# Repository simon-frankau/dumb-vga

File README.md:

# A simple flash-based VGA display

![A picture of a cat's head, surrounded by a kind of sunburst pattern,
being displayed on a montior](./demo.jpg)

The idea of this project is to generate a basic VGA-like signal that a
monitor will display by putting the signal in a flash memory, and then
using counters to run through the address space. Simple, eh?

## VGA signal timing

We have h-sync and v-sync signals, with their respective front and
back porches. The main trick is the find a resolution that fits nicely
into a flash memory, so that the flash memory is a multiple of the
screen size - not the visible screen size, but the screen size with
all the sync bits.

A bit of twiddling gives a 384x240 visible display that is 512x256
once all the sync etc. is factored in.

## Clocking

A 32MHz clock is used as a dot clock for a 768x480 image at 60 FPS
(1024x512 when sync signals are factored in). The Flash cannot handle
a 32MHz data rate, but we clock it every other cycle and do scan-line
doubling to display a 384x240 image.

## VGA levels

H- and V-sync signals are straightforward to produce, as they're
apparently supposed to be TTL. That leaves 6 bits for 3 channels of
colour, or 2 bits per channel. A pair of resistors on each channel
makes the world's simplest DAC, with values chosen to give a 0.7V peak
when terminated by a 75 ohm resistor when both bits are set.

## Test pattern

gen_test.lua generates a simple RGB "checkerboard" displaying the
range of available colours.

gen_rom.lua generates a ROM image given a Gimp .data file (I couldn't
find a nice low-dep Lua image library). It simply takes the top two
bits of each pixel value to generate the colour.

prep_img.lua converts a .data image into another .data image that uses
the 6-bit colour space that the circuit can display. It uses dithering
to improve the generated image. Generating a ROM image from an image
that has been prepared with 'prep_img' should produce a rather better
result.

## Circuit design

The circuit breadboarded so far has three chained 74HC counters
supplying the address to a 29040 flash chip. A 74HC574 latches the
values for the display. (A 74HC574 triggers on the wrong edge to avoid
transients, but it's what I had to hand, and seems to work fine.)

## PCB

I sent the files in hw/gerbers to http://smart-prototyping.com/, and
they quickly sent me back PCBs which did the job. There are PDFs of
the Gerbers in hw/images.

### Assembly notes

The PCB is pretty straightforward to assemble (no surface mount!) as
long as you pay attention to the orientations, as I oriented things to
make routing easy, rather than assembly.

There should be enough space for a ZIF for the flash chip, although I
only used an IC socket.

The PCB has been designed to support 8-pin-sized oscillators as well
as 14-pin-sized oscillators. However, I installed the larger size.
Take a careful look at the PCB to see how to install the smaller
crystal if that's what you have. Check that power and ground reach the
appropriate pins.

Note that pin 1 of the power connector is ground, and pin 3 is Vcc.
This is something I wasn't paying attention to when setting up the
schematic (nor did I label it on the silkscreen).

### Animation speed

There are two headers on the board that you can jumper to set the
animation speed. They look like this:

```
 . . .   . . .
   P3      P2
```

The possibilities are:

```
 === .   === . Slow

 === .   . === Medium

 . ===   . === Fast
```

Note that only "medium" displays the 4 frames in the order they are in
memory (i.e. 1 2 3 4 1 2 3 4 ...). In the other two modes, the order
is 1 3 2 4 1 3 2 4 ... (if you're wondering why, it's because the
2-bit counter is bit-reversed). You will need to take this into
account when programming your animations.

## ROM image generation

The 'build.sh' script will generate a nice spinny [Bad Advice
cat](http://knowyourmeme.com/memes/bad-advice-cat) ROM image. If
you're using medium-speed mode, you'll need to pass the 'swap' flag.

I was originally hoping to script up the image wrangling mostly in
Gimp, but it turns out the script-fu support is rubbish. You can't
even [load a raw .data file in a non-interactive
script](https://github.com/marcelteun/GIMP-raw-file-load/blob/5f02e7607b1645d54b11bb9f01d44e362abca2d1/file-raw-load.c#L237).
So, it's just raw data files.

cat.data.gz was generated from cat.png using the Gimp interactively.
Which was me just scrubbing the background off the Bad Advice Cat
image. Minor copyright infringement is probably involved.

If you want to create your own image, I'm sure you can work out how to
do it by looking at build.sh and the lua scripts.

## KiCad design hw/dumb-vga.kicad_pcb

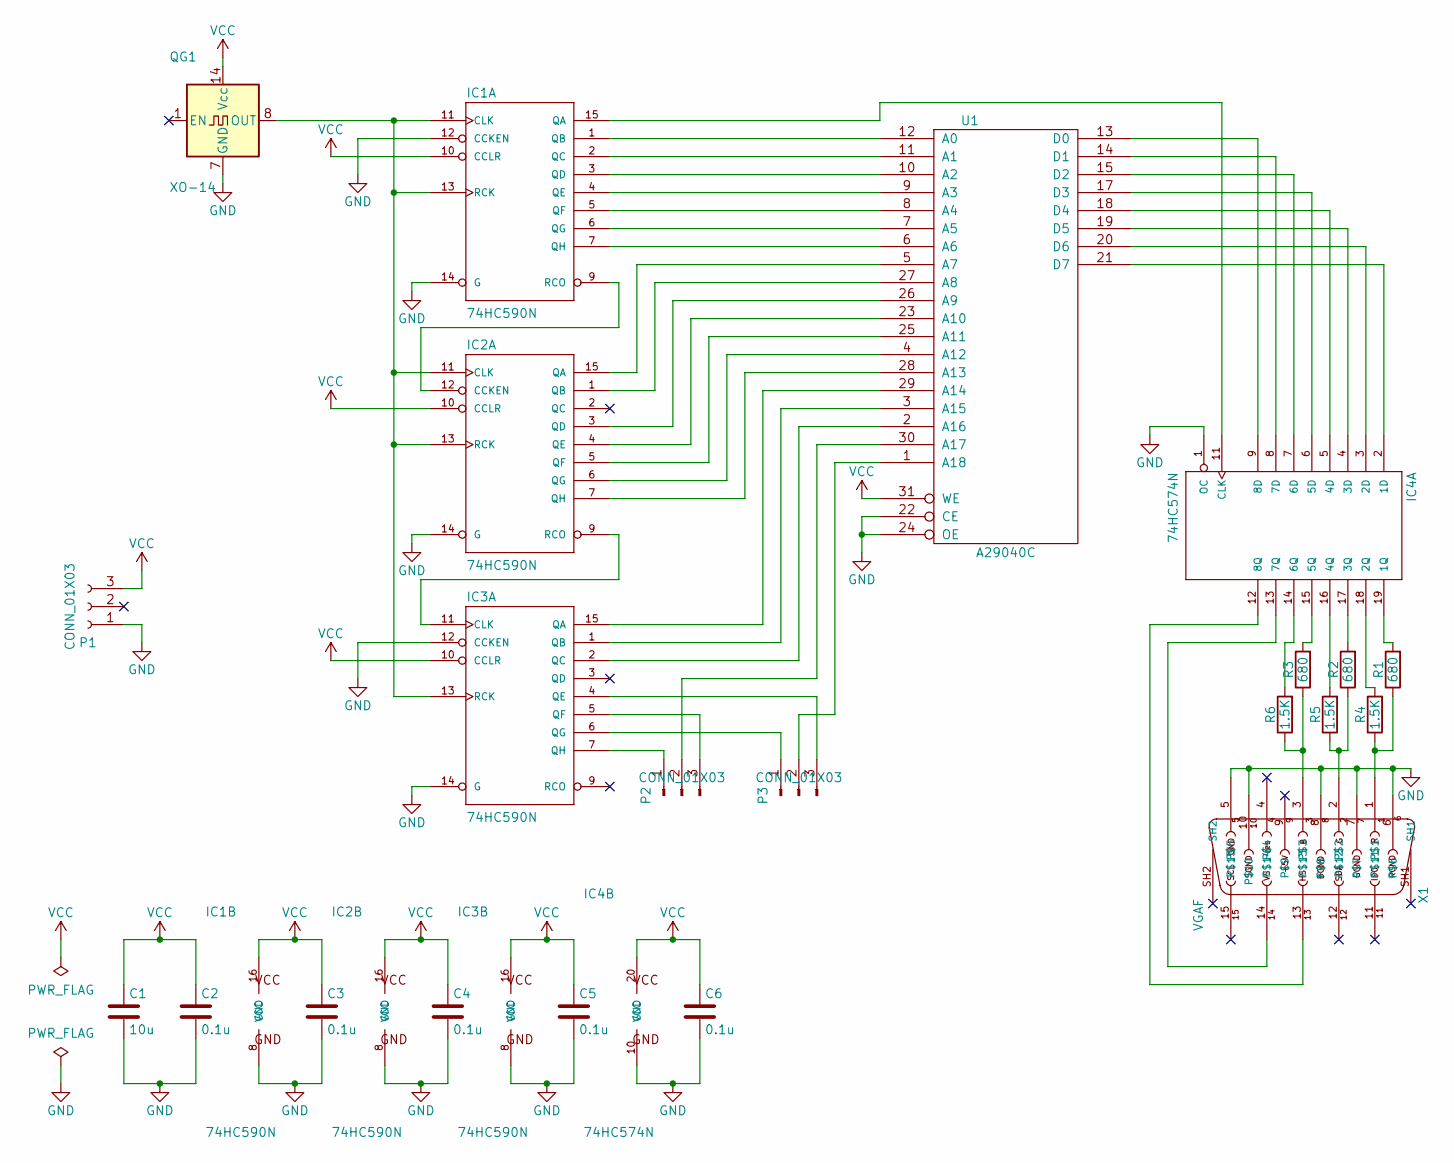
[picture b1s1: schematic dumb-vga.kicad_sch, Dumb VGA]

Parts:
C1: 10u; C_Rect_L7_W2.5_P5
C2, C3, C4, C5, C6: 0.1u; C_Rect_L7_W2.5_P5
IC1, IC2, IC3: 74HC590N; DIP-16_W7.62mm
IC4: 74HC574N; DIP-20_W7.62mm
P1: CONN_01X03; Pin_Header_Angled_1x03
P2, P3: CONN_01X03; Pin_Header_Straight_1x03
QG1: XO-14; xo-8-14
R1, R2, R3: 680; Resistor_Horizontal_RM10mm
R4, R5, R6: 1.5K; Resistor_Horizontal_RM10mm
U1: A29040C; DIP-32_W15.24mm
X1: VGAF; hd15f

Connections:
GND: C1.2, C2.2, C3.2, C4.2, C5.2, C6.2, IC1.8 (GND), IC1.12 (CCKEN), IC1.14 (G), IC2.8 (GND), IC2.14 (G), IC3.8 (GND), IC3.12 (CCKEN), IC3.14 (G), IC4.1 (OC), IC4.10 (GND), P1.1, QG1.7 (GND), U1.16 (GND), U1.22 (CE), U1.24 (OE), X1.5, X1.6, X1.7, X1.8, X1.10
unnamed: IC1.11 (CLK), IC1.13 (RCK), IC2.11 (CLK), IC2.13 (RCK), IC3.13 (RCK), QG1.8 (OUT)
unnamed: IC1.15 (QA), IC4.11 (CLK)
unnamed: IC1.1 (QB), U1.12 (A0)
unnamed: IC1.2 (QC), U1.11 (A1)
unnamed: IC1.3 (QD), U1.10 (A2)
unnamed: IC1.4 (QE), U1.9 (A3)
unnamed: IC1.5 (QF), U1.8 (A4)
unnamed: IC1.6 (QG), U1.7 (A5)
unnamed: IC1.7 (QH), U1.6 (A6)
unnamed: IC1.9 (RCO), IC2.12 (CCKEN)
unnamed: IC2.15 (QA), U1.5 (A7)
unnamed: IC2.1 (QB), U1.27 (A8)
unnamed: IC2.3 (QD), U1.26 (A9)
unnamed: IC2.4 (QE), U1.23 (A10)
unnamed: IC2.5 (QF), U1.25 (A11)
unnamed: IC2.6 (QG), U1.4 (A12)
unnamed: IC2.7 (QH), U1.28 (A13)
unnamed: IC2.9 (RCO), IC3.11 (CLK)
unnamed: IC3.15 (QA), U1.29 (A14)
unnamed: IC3.1 (QB), U1.3 (A15)
unnamed: IC3.2 (QC), U1.2 (A16)
unnamed: IC3.4 (QE), P3.3
unnamed: IC3.5 (QF), P2.3
unnamed: IC3.6 (QG), P3.1
unnamed: IC3.7 (QH), P2.1
unnamed: IC4.2 (1D), U1.21 (D7)
unnamed: IC4.19 (1Q), R1.2
unnamed: IC4.3 (2D), U1.20 (D6)
unnamed: IC4.18 (2Q), R4.2
unnamed: IC4.4 (3D), U1.19 (D5)
unnamed: IC4.17 (3Q), R2.2
unnamed: IC4.5 (4D), U1.18 (D4)
unnamed: IC4.16 (4Q), R5.2
unnamed: IC4.6 (5D), U1.17 (D3)
unnamed: IC4.15 (5Q), R3.2
unnamed: IC4.7 (6D), U1.15 (D2)
unnamed: IC4.14 (6Q), R6.2
unnamed: IC4.8 (7D), U1.14 (D1)
unnamed: IC4.13 (7Q), X1.14
unnamed: IC4.9 (8D), U1.13 (D0)
unnamed: IC4.12 (8Q), X1.13
unnamed: P2.2, U1.30 (A17)
unnamed: P3.2, U1.1 (A18)
unnamed: R1.1, R4.1, X1.1
unnamed: R2.1, R5.1, X1.2
unnamed: R3.1, R6.1, X1.3
VCC: C1.1, C2.1, C3.1, C4.1, C5.1, C6.1, IC1.10 (CCLR), IC1.16 (VCC), IC2.10 (CCLR), IC2.16 (VCC), IC3.10 (CCLR), IC3.16 (VCC), IC4.20 (VCC), P1.3, QG1.14 (Vcc), U1.31 (WE), U1.32 (VCC)

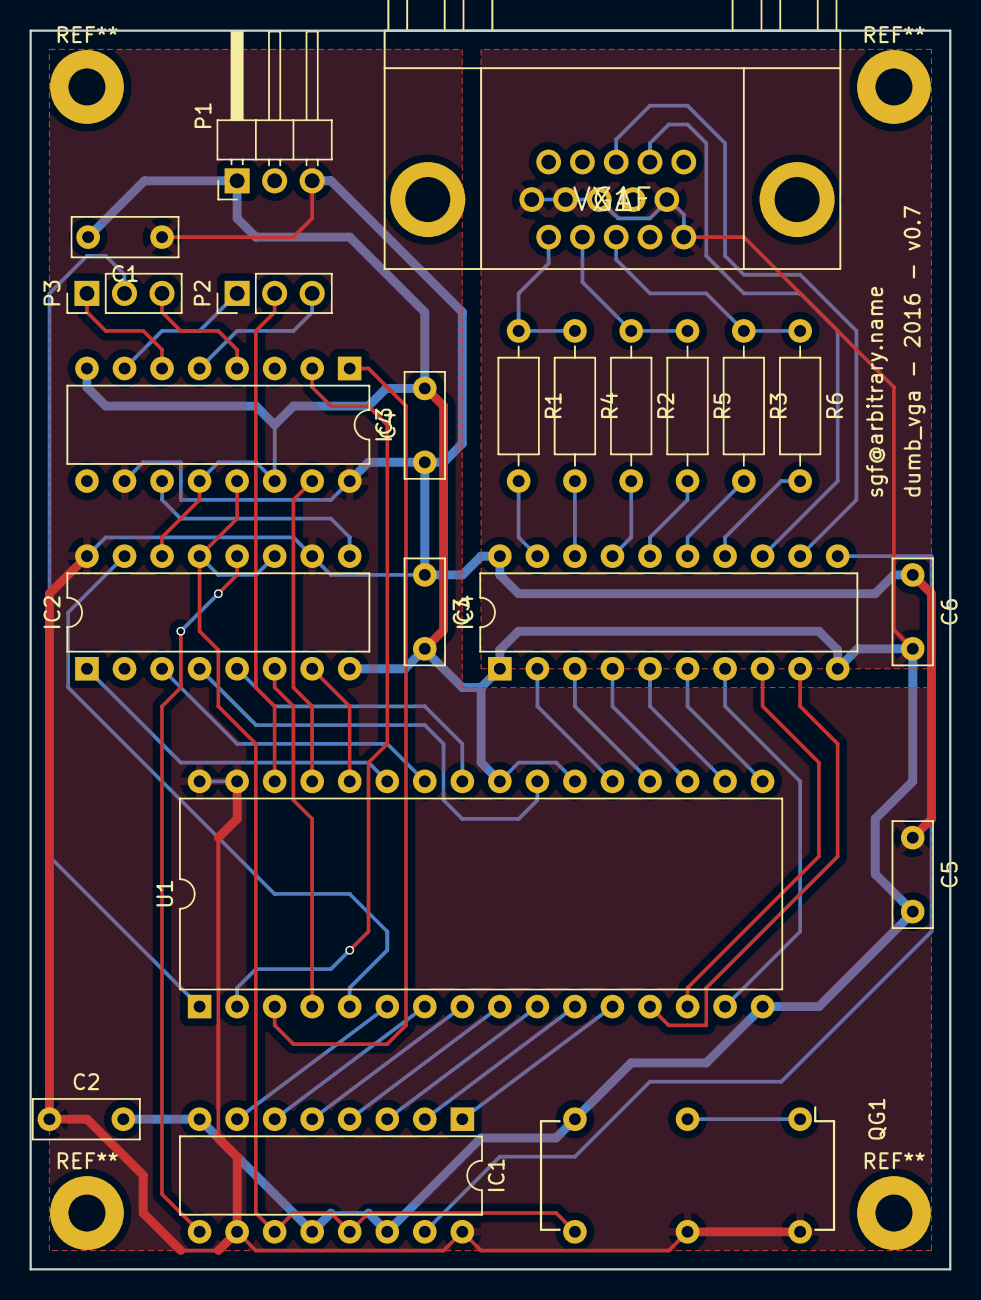
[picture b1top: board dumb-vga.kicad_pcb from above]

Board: 2 copper layers, 62.2 x 83.8 mm, 22 parts (0 on the bottom side), 48 nets.

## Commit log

2016-02-21 Generate a simple test pattern
2016-02-22 Added README.md and LICENSE
2016-02-29 Moved to a 16MHz clock
2016-02-29 Add a tool to prepare an image for transfer
2016-03-04 Add a tool to convert an image to a ROM
2016-03-05 v0 Schematic - very first circuit I built
2016-03-05 Add a .gitignore
2016-03-05 v0.1: Added 74574 buffer to eliminate black stripes
2016-03-05 Update README.md to reflect schematic changes
2016-03-06 v0.2 Upped clock speed, added animation
2016-03-06 v0.3 Moved inverter
2016-03-06 Eliminated inverter
2016-03-09 Updated README to current status of the project
2016-03-09 FIXME: Scan-line doubling
2016-03-15 Add scan-line doubling
2016-03-15 Add control over animation rate
2016-03-15 Add note to improve resistor selection for better colour range
2016-03-15 Add radial pattern generator
2016-03-16 Tweak README with todos
2016-03-16 Make animation rate switchable
2016-03-16 Starting to design the PCB
2016-03-16 Rearranged memory lines to make PCB layout easier, laid out more PCB.
2016-03-16 Changed power connector for something I have
2016-03-17 PCB tidy-up
2016-03-17 Update TODO items again
2016-03-18 Bumping schematic version number, labelling up PCB
2016-03-19 Switched to VGA connector with soldermask on the bottom
2016-03-19 Add generated Gerbers (set up for smart-prototyping.com)
2016-04-06 Switch resistors around to make programming easier
2016-04-06 Fixed scripts to work with final PCB design
2016-04-06 Update LICENSE years
2016-04-06 Update README.md in the face of practical PCB-assembly experience
2016-08-13 Start scripting up the generation of the ROM
2016-08-13 Add the other part of the image generation
2016-08-13 Add support for middle-speed ROM image
2016-08-13 Rearrange the directory structure a little
2016-08-13 Add README docs for image generation
2016-08-13 Remove extra, unnecessary, slow-loading libraries from the kicad .pro file.
2016-08-13 Hang on, it's README.md, not README.html.
2023-09-08 Update to new version of Kicad
2023-09-08 Move away from custom symbols, where convenient.
    Upgrading from an ancient version of Kicad left me with a bunch of
    symbosls in a local library that overlapped with the standard
    library. For the easy cases, I've tried to switch over. Where it would
    require rearranging lines on the schematic, I have not bothered.
2023-09-08 Move PCB onto standard footprints
2023-09-08 Update project-specific library
2023-09-08 Rename the library, to no longer be "rescue".
2023-09-10 Get rid of unused cache lib, update CHANGELOG
2023-09-10 Update Gerbers
2023-09-10 Ooops, update version in schematic, too.
2023-09-10 Add images, update README.md
